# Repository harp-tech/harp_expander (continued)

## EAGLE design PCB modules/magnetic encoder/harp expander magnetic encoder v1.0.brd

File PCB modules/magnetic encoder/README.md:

# Harp Expander Magnetic Encoder

## Licensing

The designs, documentation, and photos available in this repository are free: you can redistribute it and/or modify it under the terms of the used license.
Check file named LICENSE.

Copyright Filipe Carvalho 2020-2021

<br />This work is licensed under a <a rel="license" href="http://creativecommons.org/licenses/by-nc-sa/3.0/igo/">Creative Commons Attribution-NonCommercial-ShareAlike 3.0 IGO License</a>.

If your are interested in obtaining a license to sell this device, please contact filipe@open-ephys.org

[1]: https://docs.google.com/spreadsheets/d/1aobmmEzBDethzIlrm1eg0eYkBqlyX3s9WbA9KgRwVQI/edit?usp=sharing

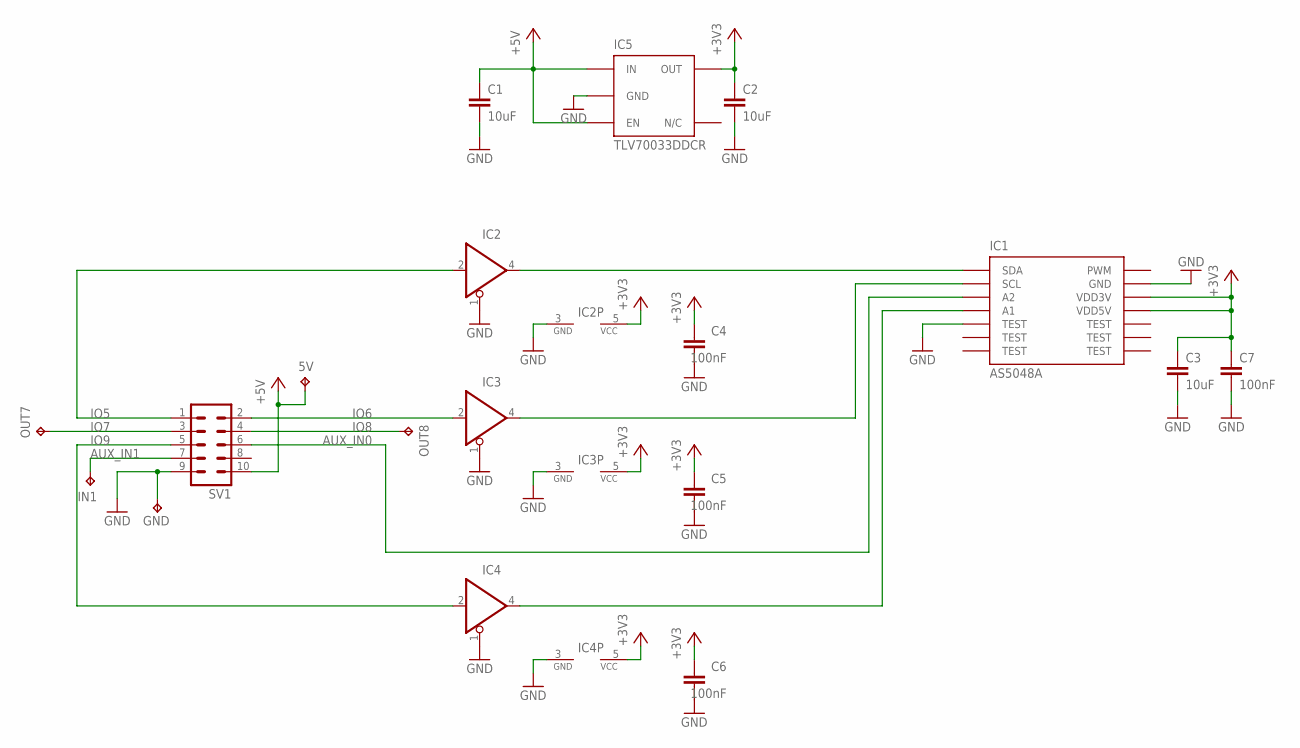
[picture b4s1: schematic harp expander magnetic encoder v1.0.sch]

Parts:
5V: TPPAD1-13; P1-13
C1, C2, C3: 10uF; C0603; MPN C1608X6S1C475K080AC
C4, C5, C6, C7: 100nF; C0402; MPN MC0402B104K160CT
GND: TPPAD1-13; P1-13
IC1: AS5048A; TSSOP-14
IC2, IC3, IC4: SN74LVC1G125DBVT; SOT23-5; MPN SN74LVC1G125DBVT
IC5: TLV70033DDCR; TSOT23-5; MPN TLV70033DDCR
IN1: TPPAD1-13; P1-13
OUT7, OUT8: TPPAD1-13; P1-13
SV1: ML10

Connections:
!CS: IC1.1 (SDA), IC2.4 (O)
+3V3: C2.1, C3.1, C4.1, C5.1, C6.1, C7.1, IC1.11 (VDD5V), IC1.12 (VDD3V), IC2.5 (VCC), IC3.5 (VCC), IC4.5 (VCC), IC5.5 (OUT)
+5V: 5V.TP, C1.1, IC5.1 (IN), IC5.3 (EN), SV1.10
AUX_IN0: IC1.3 (A2), SV1.6
AUX_IN1: IN1.TP, SV1.7
CLK: IC1.2 (SCL), IC3.4 (O)
GND: C1.2, C2.2, C3.2, C4.2, C5.2, C6.2, C7.2, GND.TP, IC1.5 (TEST), IC1.13 (GND), IC2.1 (OE), IC2.3 (GND), IC3.1 (OE), IC3.3 (GND), IC4.1 (OE), IC4.3 (GND), IC5.2 (GND), SV1.9
IO5: IC2.2 (I), SV1.1
IO6: IC3.2 (I), SV1.2
IO7: OUT7.TP, SV1.3
IO8: OUT8.TP, SV1.4
IO9: IC4.2 (I), SV1.5
MOSI: IC1.4 (A1), IC4.4 (O)

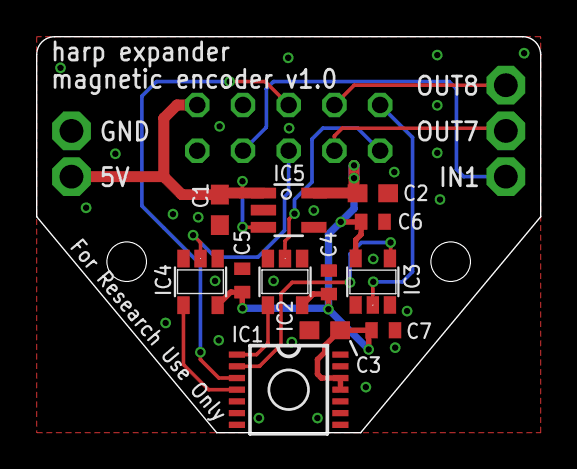
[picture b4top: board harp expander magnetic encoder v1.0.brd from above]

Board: 2 copper layers, 28.0 x 22.0 mm, 18 parts (1 on the bottom side), 13 nets.

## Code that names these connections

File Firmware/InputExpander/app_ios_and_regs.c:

#include <avr/io.h>
#include "hwbp_core_types.h"
#include "app_ios_and_regs.h"

/************************************************************************/
/* Configure and initialize IOs                                         */
/************************************************************************/
void init_ios(void)
{	/* Configure input pins */
	io_pin2in(&PORTE, 2, PULL_IO_TRISTATE, SENSE_IO_EDGES_BOTH);         // AUX_INPUT0
	io_pin2in(&PORTE, 5, PULL_IO_TRISTATE, SENSE_IO_EDGES_BOTH);         // AUX_INPUT1
	io_pin2in(&PORTE, 3, PULL_IO_UP, SENSE_IO_EDGES_BOTH);               // IS_INPUT
	io_pin2in(&PORTD, 4, PULL_IO_TRISTATE, SENSE_IO_EDGES_BOTH);         // IN0
	io_pin2in(&PORTD, 3, PULL_IO_TRISTATE, SENSE_IO_EDGES_BOTH);         // IN1
	io_pin2in(&PORTD, 2, PULL_IO_TRISTATE, SENSE_IO_EDGES_BOTH);         // IN2
	io_pin2in(&PORTD, 1, PULL_IO_TRISTATE, SENSE_IO_EDGES_BOTH);         // IN3
	io_pin2in(&PORTD, 0, PULL_IO_TRISTATE, SENSE_IO_EDGES_BOTH);         // IN4
	io_pin2in(&PORTC, 0, PULL_IO_TRISTATE, SENSE_IO_EDGES_BOTH);         // IN5
	io_pin2in(&PORTC, 1, PULL_IO_TRISTATE, SENSE_IO_EDGES_BOTH);         // IN6
	io_pin2in(&PORTC, 2, PULL_IO_TRISTATE, SENSE_IO_EDGES_BOTH);         // IN7
	io_pin2in(&PORTC, 3, PULL_IO_TRISTATE, SENSE_IO_EDGES_BOTH);         // IN8
	io_pin2in(&PORTE, 0, PULL_IO_TRISTATE, SENSE_IO_EDGES_BOTH);         // IN9
	io_pin2in(&PORTA, 0, PULL_IO_DOWN, SENSE_IO_EDGES_BOTH);             // PA0
	io_pin2in(&PORTA, 1, PULL_IO_DOWN, SENSE_IO_EDGES_BOTH);             // PA1
	io_pin2in(&PORTA, 2, PULL_IO_DOWN, SENSE_IO_EDGES_BOTH);             // PA2
	io_pin2in(&PORTA, 3, PULL_IO_DOWN, SENSE_IO_EDGES_BOTH);             // PA3
	io_pin2in(&PORTA, 4, PULL_IO_DOWN, SENSE_IO_EDGES_BOTH);             // PA4
	io_pin2in(&PORTA, 5, PULL_IO_DOWN, SENSE_IO_EDGES_BOTH);             // PA5
	io_pin2in(&PORTA, 7, PULL_IO_DOWN, SENSE_IO_EDGES_BOTH);             // PA7
	io_pin2in(&PORTB, 0, PULL_IO_DOWN, SENSE_IO_EDGES_BOTH);             // PB0
	io_pin2in(&PORTB, 1, PULL_IO_DOWN, SENSE_IO_EDGES_BOTH);             // PB1
	io_pin2in(&PORTB, 2, PULL_IO_DOWN, SENSE_IO_EDGES_BOTH);             // PB2
	io_pin2in(&PORTB, 3, PULL_IO_DOWN, SENSE_IO_EDGES_BOTH);             // PB3
	io_pin2in(&PORTB, 4, PULL_IO_DOWN, SENSE_IO_EDGES_BOTH);             // PB4
	io_pin2in(&PORTB, 7, PULL_IO_DOWN, SENSE_IO_EDGES_BOTH);             // PB7
	io_pin2in(&PORTC, 4, PULL_IO_DOWN, SENSE_IO_EDGES_BOTH);             // PC4
	io_pin2in(&PORTC, 5, PULL_IO_DOWN, SENSE_IO_EDGES_BOTH);             // PC5
	io_pin2in(&PORTD, 5, PULL_IO_DOWN, SENSE_IO_EDGES_BOTH);             // PD5
	io_pin2in(&PORTE, 1, PULL_IO_DOWN, SENSE_IO_EDGES_BOTH);             // PE1
	io_pin2in(&PORTE, 6, PULL_IO_DOWN, SENSE_IO_EDGES_BOTH);             // PE6
	io_pin2in(&PORTE, 7, PULL_IO_DOWN, SENSE_IO_EDGES_BOTH);             // PE7
	io_pin2in(&PORTF, 0, PULL_IO_DOWN, SENSE_IO_EDGES_BOTH);             // PF0
	io_pin2in(&PORTF, 1, PULL_IO_DOWN, SENSE_IO_EDGES_BOTH);             // PF1
	io_pin2in(&PORTF, 4, PULL_IO_DOWN, SENSE_IO_EDGES_BOTH);             // PF4
	io_pin2in(&PORTF, 5, PULL_IO_DOWN, SENSE_IO_EDGES_BOTH);             // PF5
	io_pin2in(&PORTF, 6, PULL_IO_DOWN, SENSE_IO_EDGES_BOTH);             // PF6
	io_pin2in(&PORTF, 7, PULL_IO_DOWN, SENSE_IO_EDGES_BOTH);             // PF7
	io_pin2in(&PORTJ, 3, PULL_IO_DOWN, SENSE_IO_EDGES_BOTH);             // PJ3
	io_pin2in(&PORTJ, 4, PULL_IO_DOWN, SENSE_IO_EDGES_BOTH);             // PJ4
	io_pin2in(&PORTJ, 5, PULL_IO_DOWN, SENSE_IO_EDGES_BOTH);             // PJ5
	io_pin2in(&PORTJ, 7, PULL_IO_DOWN, SENSE_IO_EDGES_BOTH);             // PJ7
	io_pin2in(&PORTK, 3, PULL_IO_DOWN, SENSE_IO_EDGES_BOTH);             // PK3
	io_pin2in(&PORTK, 4, PULL_IO_DOWN, SENSE_IO_EDGES_BOTH);             // PK4
	io_pin2in(&PORTK, 5, PULL_IO_DOWN, SENSE_IO_EDGES_BOTH);             // PK5
	io_pin2in(&PORTK, 6, PULL_IO_DOWN, SENSE_IO_EDGES_BOTH);             // PK6
	io_pin2in(&PORTK, 7, PULL_IO_DOWN, SENSE_IO_EDGES_BOTH);             // PK7
	io_pin2in(&PORTQ, 0, PULL_IO_DOWN, SENSE_IO_EDGES_BOTH);             // PQ0
	io_pin2in(&PORTQ, 1, PULL_IO_DOWN, SENSE_IO_EDGES_BOTH);             // PQ1
	io_pin2in(&PORTQ, 2, PULL_IO_DOWN, SENSE_IO_EDGES_BOTH);             // PQ2
	io_pin2in(&PORTQ, 3, PULL_IO_DOWN, SENSE_IO_EDGES_BOTH);             // PQ3

	/* Configure input interrupts */
	io_set_int(&PORTE, INT_LEVEL_LOW, 0, (1<<2), false);                 // AUX_INPUT0
	io_set_int(&PORTE, INT_LEVEL_LOW, 0, (1<<5), false);                 // AUX_INPUT1
	io_set_int(&PORTD, INT_LEVEL_LOW, 0, (1<<4), false);                 // IN0
	io_set_int(&PORTD, INT_LEVEL_LOW, 0, (1<<3), false);                 // IN1
	io_set_int(&PORTD, INT_LEVEL_LOW, 0, (1<<2), false);                 // IN2
	io_set_int(&PORTD, INT_LEVEL_LOW, 0, (1<<1), false);                 // IN3
	io_set_int(&PORTD, INT_LEVEL_LOW, 0, (1<<0), false);                 // IN4
	io_set_int(&PORTC, INT_LEVEL_LOW, 0, (1<<0), false);                 // IN5
	io_set_int(&PORTC, INT_LEVEL_LOW, 0, (1<<1), false);                 // IN6
	io_set_int(&PORTC, INT_LEVEL_LOW, 0, (1<<2), false);                 // IN7
	io_set_int(&PORTC, INT_LEVEL_LOW, 0, (1<<3), false);                 // IN8
	io_set_int(&PORTE, INT_LEVEL_LOW, 1, (1<<0), false);                 // IN9

	/* Configure output pins */
	io_pin2out(&PORTH, 0, OUT_IO_DIGITAL, IN_EN_IO_EN);                  // LED_0
	io_pin2out(&PORTH, 1, OUT_IO_DIGITAL, IN_EN_IO_EN);                  // LED_1
	io_pin2out(&PORTH, 2, OUT_IO_DIGITAL, IN_EN_IO_EN);                  // LED_2
	io_pin2out(&PORTH, 3, OUT_IO_DIGITAL, IN_EN_IO_EN);                  // LED_3
	io_pin2out(&PORTH, 4, OUT_IO_DIGITAL, IN_EN_IO_EN);                  // LED_4
	io_pin2out(&PORTH, 5, OUT_IO_DIGITAL, IN_EN_IO_EN);                  // LED_5
	io_pin2out(&PORTH, 6, OUT_IO_DIGITAL, IN_EN_IO_EN);                  // LED_6
	io_pin2out(&PORTH, 7, OUT_IO_DIGITAL, IN_EN_IO_EN);                  // LED_7
	io_pin2out(&PORTJ, 0, OUT_IO_DIGITAL, IN_EN_IO_EN);                  // LED_8
	io_pin2out(&PORTJ, 1, OUT_IO_DIGITAL, IN_EN_IO_EN);                  // LED_9
	io_pin2out(&PORTJ, 2, OUT_IO_DIGITAL, IN_EN_IO_EN);                  // LED_PWR
	io_pin2out(&PORTA, 6, OUT_IO_DIGITAL, IN_EN_IO_EN);                  // LED_STATE
	io_pin2out(&PORTB, 5, OUT_IO_DIGITAL, IN_EN_IO_EN);                  // IDE_IOS_DIR
	io_pin2out(&PORTB, 6, OUT_IO_DIGITAL, IN_EN_IO_EN);                  // IDE_IOS_EN
	io_pin2out(&PORTD, 7, OUT_IO_DIGITAL, IN_EN_IO_EN);                  // BNC_IOS_DIR
	io_pin2out(&PORTD, 6, OUT_IO_DIGITAL, IN_EN_IO_EN);                  // BNC_IOS_EN

	/* Initialize output pins */
	clr_LED_0;
	clr_LED_1;
	clr_LED_2;
	clr_LED_3;
	clr_LED_4;
	clr_LED_5;
	clr_LED_6;
	clr_LED_7;
	clr_LED_8;
	clr_LED_9;
	clr_LED_PWR;
	clr_LED_STATE;
	set_IDE_IOS_DIR;
	clr_IDE_IOS_EN;
	set_BNC_IOS_DIR;
	clr_BNC_IOS_EN;
}

/************************************************************************/
/* Registers' stuff                                                     */
/************************************************************************/
AppRegs app_regs;

uint8_t app_regs_type[] = {
	TYPE_U8,
	TYPE_U8,
	TYPE_U8,
	TYPE_U16,
	TYPE_U16,
	TYPE_U16,
	TYPE_U8,
	TYPE_U8,
	TYPE_I16,
	TYPE_U8
};

uint16_t app_regs_n_elements[] = {
	1,
	1,
	1,
	2,
	1,
	1,
	1,
	1,
	1,
	1
};

uint8_t *app_regs_pointer[] = {
	(uint8_t*)(&app_regs.REG_AUX_INPUTS),
	(uint8_t*)(&app_regs.REG_AUX_INPUTS_RISING_EDGE_ENABLE),
	(uint8_t*)(&app_regs.REG_AUX_INPUTS_FALLING_EDGE_ENABLE),
	(uint8_t*)(app_regs.REG_INPUTS),
	(uint8_t*)(&app_regs.REG_RISING_EDGE_ENABLE),
	(uint8_t*)(&app_regs.REG_FALLING_EDGE_ENABLE),
	(uint8_t*)(&app_regs.REG_INPUT_MODE),
	(uint8_t*)(&app_regs.REG_ENCODER_MODE),
	(uint8_t*)(&app_regs.REG_ENCODER),
	(uint8_t*)(&app_regs.REG_EXPANSION_OPTIONS)
};

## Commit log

2020-10-18 Added the first PCB files.
2020-10-31 Updated design files to the latest version.
2020-10-31 Added gerbers, centroids and BOM.
2020-10-31 Added panels and production files.
2020-10-31 Added .gitignore.
2020-10-31 Created folders for Bonsai and Firmware.
2020-10-31 Added README and licenses.
2020-11-04 Corrected rear panel's silk screen.
2020-11-04 Added panels' gerber files.
2020-11-06 First firmware files.
2020-11-15 Added README files.
2020-11-15 Minor corrections.
2020-11-15 Added breakout v1.0.
2020-11-15 Updated BOM.
2020-11-16 Corrected pinout.
2020-11-16 Cleaned up code.
2020-11-16 Added first interrupts handling.
2020-11-21 Corrected silkscreen and minor change to top layer.
2020-12-19 Added ability to connect to a Teensy/Arduino and to read rotary encoders.
2020-12-19 Added ability to be used as a clock generator.
2020-12-19 Minor corrections on layout and schematics.
2020-12-19 Updated production files.
2020-12-20 Minor corrections to BOMs.
2021-01-02 Updated email address for commercial requests.
2021-01-02 Realocate interrupt pins to latest schematic.
2021-01-02 Corrected wrong buttons polarity.
2021-01-29 Updated files for final revision before production.
2021-01-29 Added pdf files and library.
2021-01-29 Added license.
2021-01-29 Added first magnetic encoder files.
2021-01-29 Included mechanical details for 3D design.
2021-01-29 Updated files for final revision.
2021-02-06 Updated for the first functional code (some features still to implement).
2021-02-06 Increased distance between screw connectors.
2021-02-06 Released the expander breakout PCB (v1.0).
2021-02-06 Implemented LED management.
2021-02-07 Corrected visualization and implemented the magnetic encoder expansion.
2021-02-07 Added ability to distinguish between rising and falling edges.
2021-02-07 Added code to control the expander servo driver.
2021-02-11 Changed the audio cable PN.
2021-02-11 Released expander magnetic encoder and updated expander breakout.
2021-02-11 Minor updates.
2021-02-11 Replaced oscillator with a more precise one.
2021-02-11 Added routines to facilitate the production test.
2021-02-11 Added library and updated BOM.
2021-02-16 Minor corrections to registers' descriptions.
2021-02-16 Corrected bad timing when using the servo expander.
2021-02-19 Updated license dates.
2021-02-21 Reversed the hardware's resistor assembly.
2021-02-21 Correct bad servo driver configuration.
2021-02-23 Added default for the magnetic encoder sample rate.
2021-02-24 Corrected device's ID.
2021-02-24 Released first firmware's version.
2021-03-04 Add Bonsai interface for harp expander devices
2021-03-05 Added a new version that corrects a supply noise issue and re-arranged the connector's pinout.
2021-03-07 Implemented ability to filter selected transitions on both auxiliary input lines.
2021-03-07 Added new registers to control PWM and stimulation.
2021-03-07 increased firmware version to 2.0.
2021-03-08 Created PWM and Stimulation registers.
2021-03-08 Renamed STIM registers and added PULSE registers.
2021-03-08 Added calculations for real frequency and duty cycle.
2021-03-08 Implemented the ability to produce up to 3 different PWMs.
2021-03-10 Added binary files of the most recent firmware versions.
2021-03-12 Fix #1.
2021-03-14 Fix register size
2021-03-15 Add pwm configuration and command support
2021-03-15 Extend support for pwm 1
2021-03-16 Added more flexibility to enable and disable PWM.
2021-03-16 Released firmware file for Tag OutputExpander_fw2.1-harp1.7.
2021-03-19 Ensure existing PWM state is preserved
2021-03-21 Add interface for PWM event detection
2021-03-23 Add support for configuring expansion board modes
2021-03-23 Add support for parsing angle and intensity
2021-03-23 Add support for configuring magnetic encoder mode
2021-03-23 Ensure expression build methods are static
2021-03-23 Add support for configuring the remaining PWM
2021-04-24 Added filtering on inputs and reset lines to prevent erroneous behavior in noisy environments.
2021-04-24 Added a photo of the assembled device.
2021-04-27 Added ability to read a rotary encoder.
2021-04-27 Released Input Expander firmware v2.1.
2021-05-13 Corrected bad timing when streaming the inputs state.
2021-05-13 Minor BOM correction.
2021-05-13 Released Input Expander firmware v2.2.
2021-05-31 Updated harp core to version 1.9
2021-06-01 Added version 1.2 of servo driver module.
